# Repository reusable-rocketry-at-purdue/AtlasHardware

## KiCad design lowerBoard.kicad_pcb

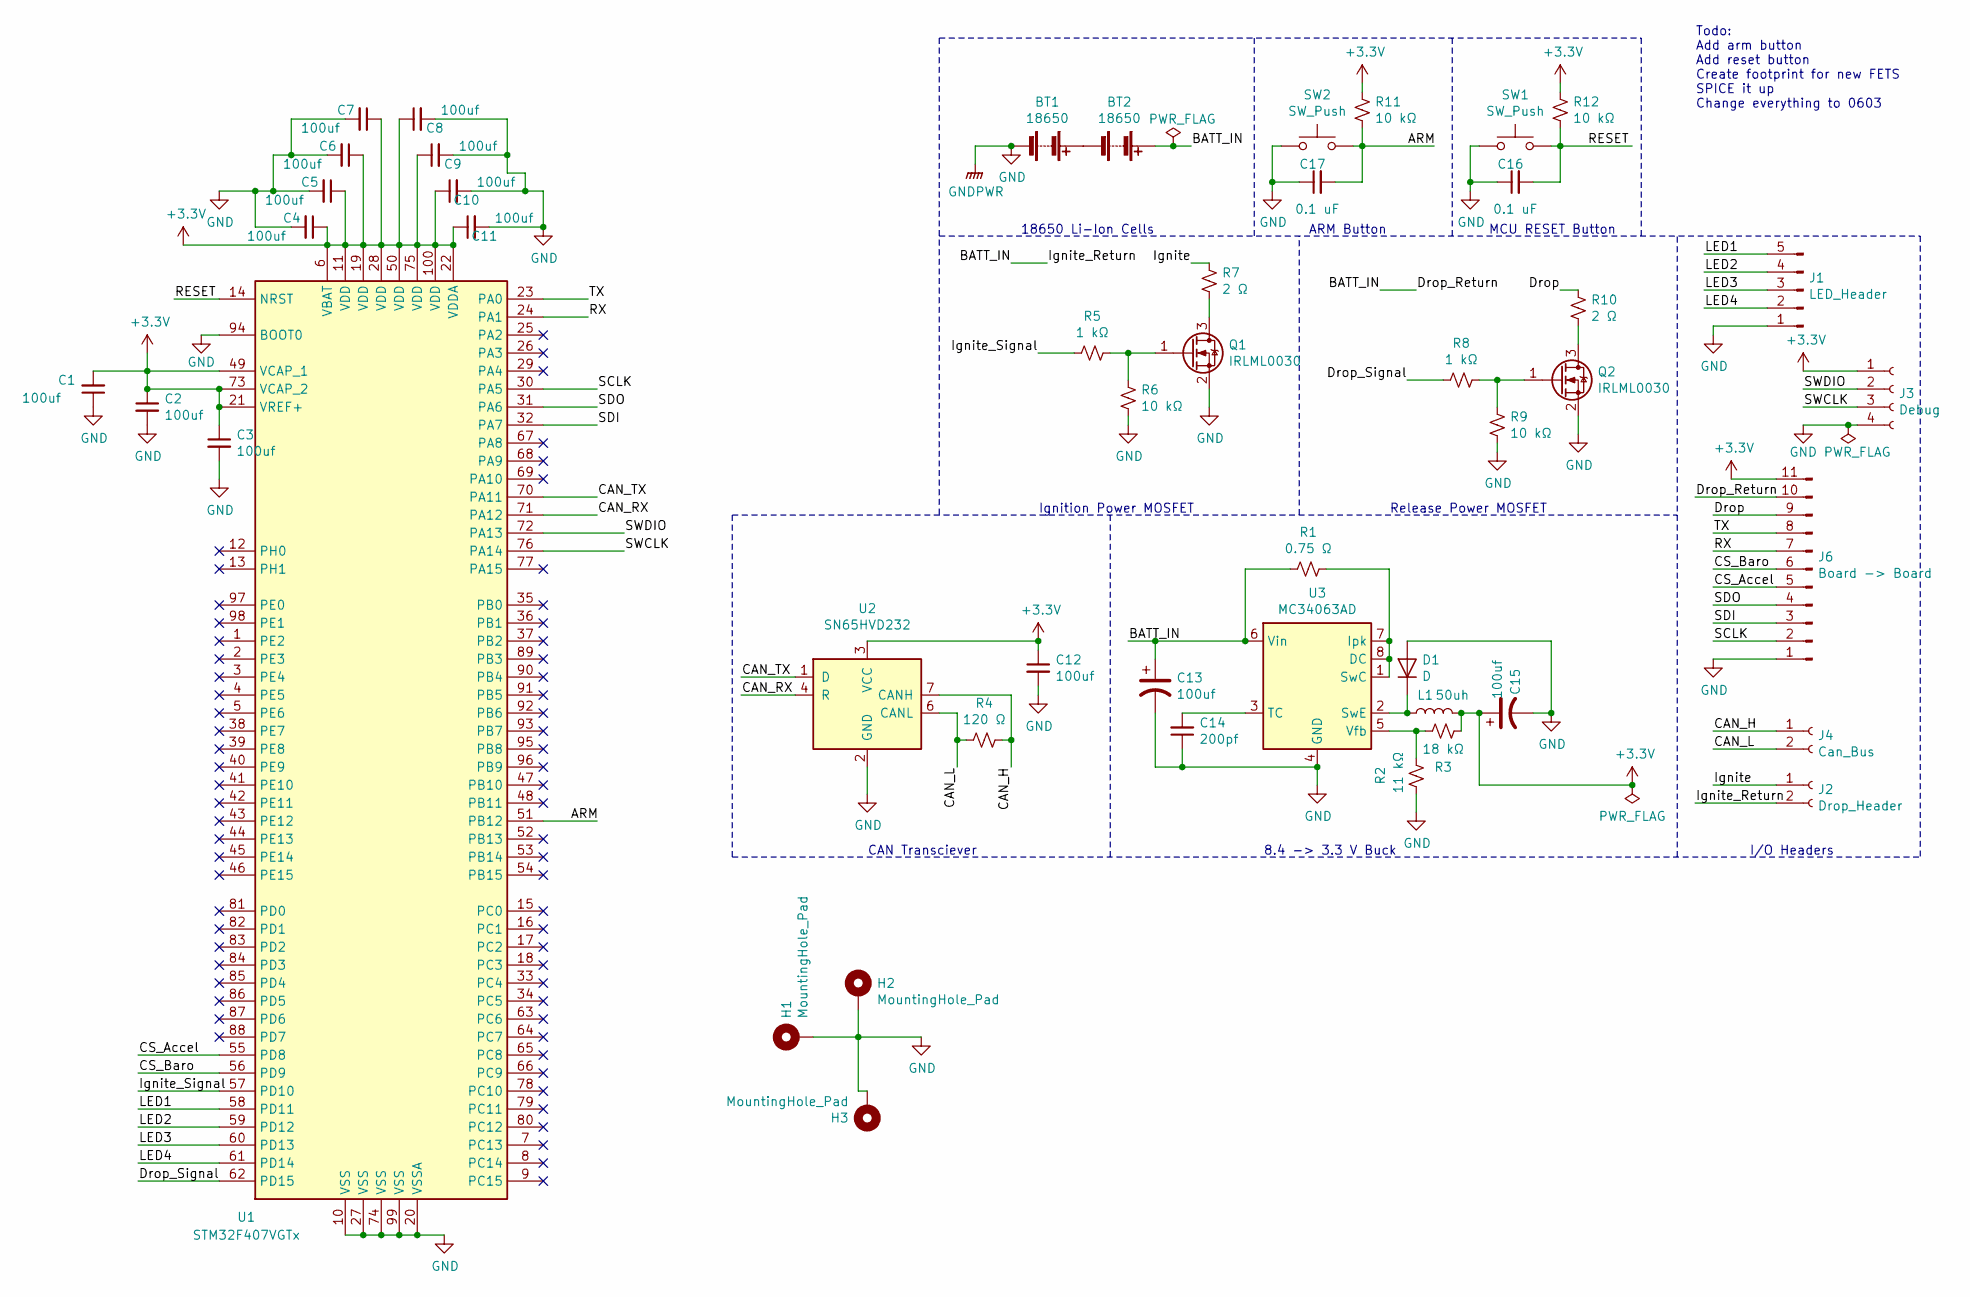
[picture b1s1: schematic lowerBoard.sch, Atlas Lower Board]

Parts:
BT1, BT2: 18650; BatteryHolder_MPD_BH-18650-PC2
C1, C2, C3, C4, C5, C6, C7, C8, C9, C10, C11, C12, C13, C15: 100uf; C_0603_1608Metric
C14: 200pf; C_0603_1608Metric
C16, C17: 0.1 uF; C_0603_1608Metric
D1: D; D_0603_1608Metric
H1, H2, H3: MountingHole_Pad; MountingHole_3mm_Pad_Via
J1: LED_Header; Molex_KK-254_AE-6410-05A_1x05_P2.54mm_Vertical
J2: Drop_Header; Molex_KK-254_AE-6410-02A_1x02_P2.54mm_Vertical
J3: Debug; Molex_KK-254_AE-6410-04A_1x04_P2.54mm_Vertical
J4: Can_Bus; Molex_KK-254_AE-6410-02A_1x02_P2.54mm_Vertical
J6: Board -> Board; Molex_KK-254_AE-6410-11A_1x11_P2.54mm_Vertical
L1: 50uh; C_0603_1608Metric
Q1, Q2: IRLML0030; SOT-23
R1: 0.75 Ω; R_0603_1608Metric
R2: 11 kΩ; R_0603_1608Metric
R3: 18 kΩ; R_0603_1608Metric
R4: 120 Ω; R_0603_1608Metric
R5, R8: 1 kΩ; R_0603_1608Metric
R6, R9, R11, R12: 10 kΩ; R_0603_1608Metric
R7, R10: 2 Ω; R_0603_1608Metric
SW1, SW2: SW_Push; SW_SPST_B3S-1000
U1: STM32F407VGTx; LQFP-100_14x14mm_P0.5mm
U2: SN65HVD232; SOIC-8_3.9x4.9mm_P1.27mm
U3: MC34063AD; SOIC-8_3.9x4.9mm_P1.27mm

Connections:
+3V3: C1.2, C2.1, C3.1, C4.1, C5.1, C6.1, C7.1, C8.1, C9.1, C10.1, C11.1, C12.1, C15.1, J3.1, J6.11, L1.2, R3.1, R11.1, R12.1, U1.6 (VBAT), U1.11 (VDD), U1.19 (VDD), U1.21 (VREF+), U1.22 (VDDA), U1.28 (VDD), U1.49 (VCAP_1), U1.50 (VDD), U1.73 (VCAP_2), U1.75 (VDD), U1.100 (VDD), U2.3 (VCC)
/ARM: C17.2, R11.2, SW2.2, U1.51 (PB12)
/BATT_IN: BT2.1 (+), C13.1, J2.2, J6.10, R1.2, U3.6 (Vin)
/CAN_H: J4.1, R4.1, U2.7 (CANH)
/CAN_L: J4.2, R4.2, U2.6 (CANL)
/CAN_RX: U1.71 (PA12), U2.4 (R)
/CAN_TX: U1.70 (PA11), U2.1 (D)
/CS_Accel: J6.5, U1.55 (PD8)
/CS_Baro: J6.6, U1.56 (PD9)
/Drop: J6.9, R10.1
/Drop_Signal: R8.2, U1.62 (PD15)
/Ignite: J2.1, R7.1
/Ignite_Signal: R5.2, U1.57 (PD10)
/LED1: J1.5, U1.58 (PD11)
/LED2: J1.4, U1.59 (PD12)
/LED3: J1.3, U1.60 (PD13)
/LED4: J1.2, U1.61 (PD14)
/RESET: C16.2, R12.2, SW1.2, U1.14 (NRST)
/RX: J6.7, U1.24 (PA1)
/SCLK: J6.2, U1.30 (PA5)
/SDI: J6.3, U1.32 (PA7)
/SDO: J6.4, U1.31 (PA6)
/SWCLK: J3.3, U1.76 (PA14)
/SWDIO: J3.2, U1.72 (PA13)
/TX: J6.8, U1.23 (PA0)
GND: BT1.2 (-), C1.1, C2.2, C3.2, C4.2, C5.2, C6.2, C7.2, C8.2, C9.2, C10.2, C11.2, C12.2, C13.2, C14.1, C15.2, C16.1, C17.1, D1.2 (A), H1.1, H2.1, H3.1, J1.1, J3.4, J6.1, Q1.2 (S), Q2.2 (S), R2.2, R6.1, R9.1, SW1.1, SW2.1, U1.10 (VSS), U1.20 (VSSA), U1.27 (VSS), U1.74 (VSS), U1.94 (BOOT0), U1.99 (VSS), U2.2 (GND), U3.4 (GND)
unnamed: BT1.1 (+), BT2.2 (-)
unnamed: C14.2, U3.3 (TC)
unnamed: D1.1 (K), L1.1, U3.2 (SwE)
unnamed: Q1.1 (G), R5.1, R6.2
unnamed: Q1.3 (D), R7.2
unnamed: Q2.1 (G), R8.1, R9.2
unnamed: Q2.3 (D), R10.2
unnamed: R1.1, U3.1 (SwC), U3.7 (Ipk), U3.8 (DC)
unnamed: R2.1, R3.2, U3.5 (Vfb)

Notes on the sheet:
18650 Li-Ion Cells
ARM Button
MCU RESET Button
Ignition Power MOSFET
Release Power MOSFET
I/O Headers
8.4 -> 3.3 V Buck
CAN Transciever
Todo: Add arm button Add reset button Create footprint for new FETS SPICE it up Change everything to 0603

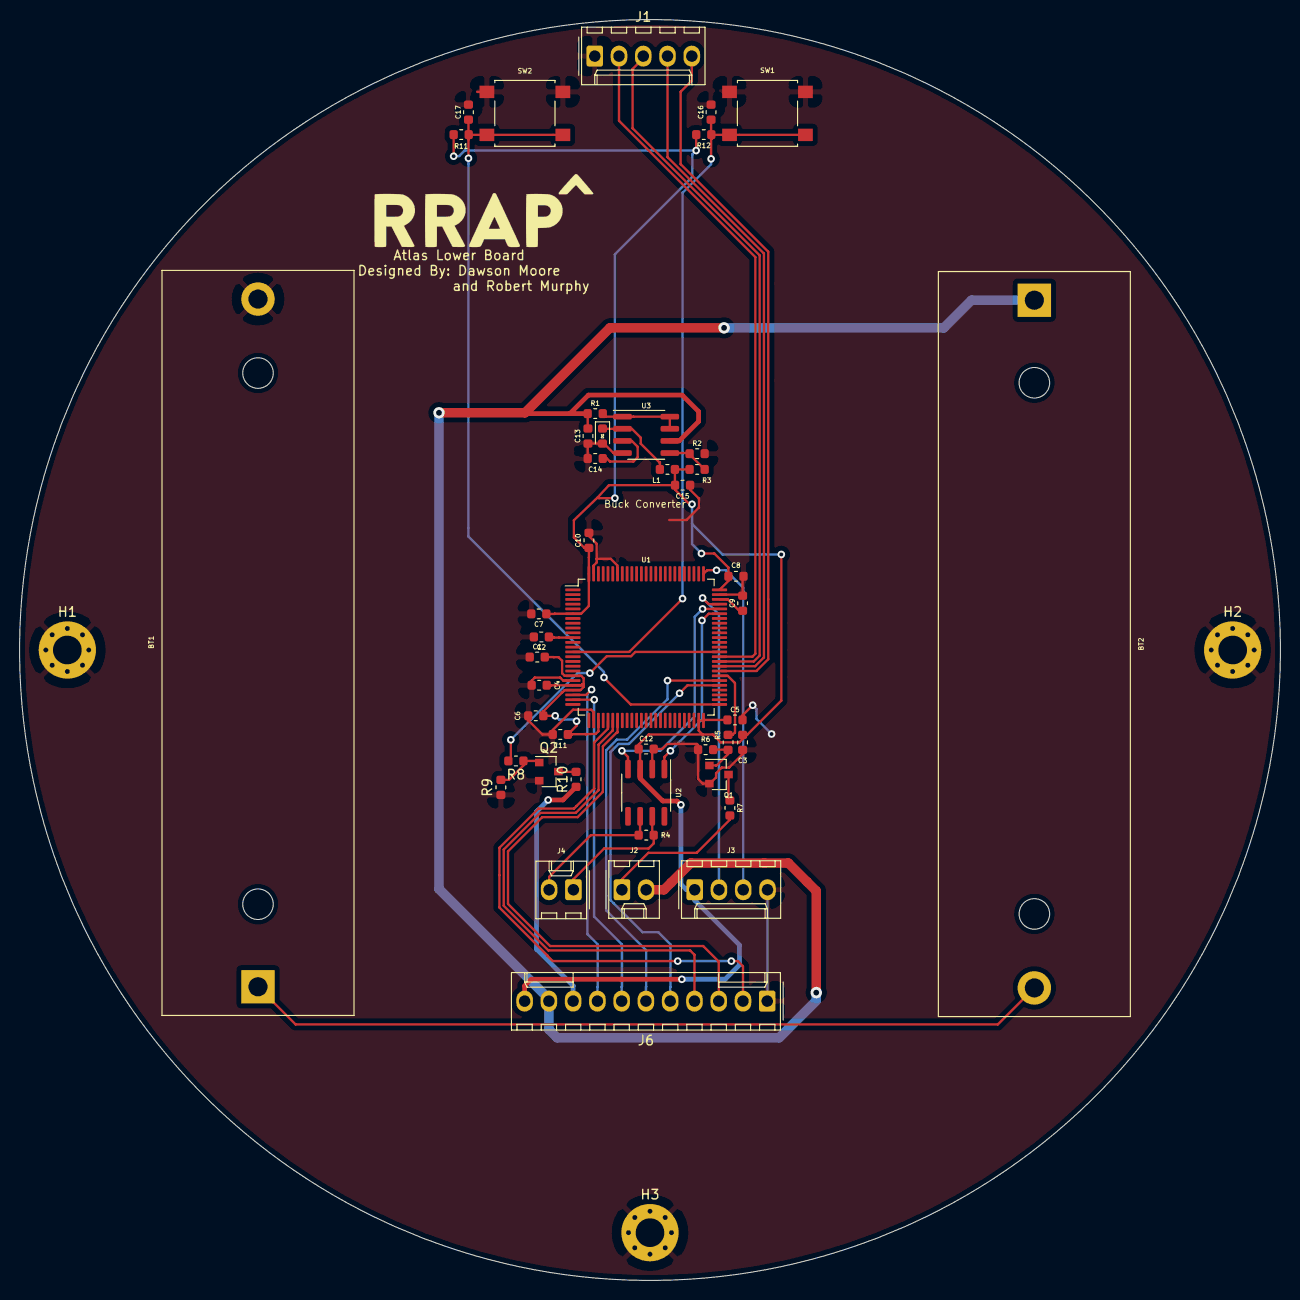
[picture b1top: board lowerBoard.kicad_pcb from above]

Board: 2 copper layers, 132.0 x 132.0 mm, 48 parts (0 on the bottom side), 35 nets.

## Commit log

2020-02-17 Added routed upper board files
2020-02-17 Add routed upper board files
2020-02-25 Gerber file for upper board
2020-02-26 Start routing and make updates to schematics
